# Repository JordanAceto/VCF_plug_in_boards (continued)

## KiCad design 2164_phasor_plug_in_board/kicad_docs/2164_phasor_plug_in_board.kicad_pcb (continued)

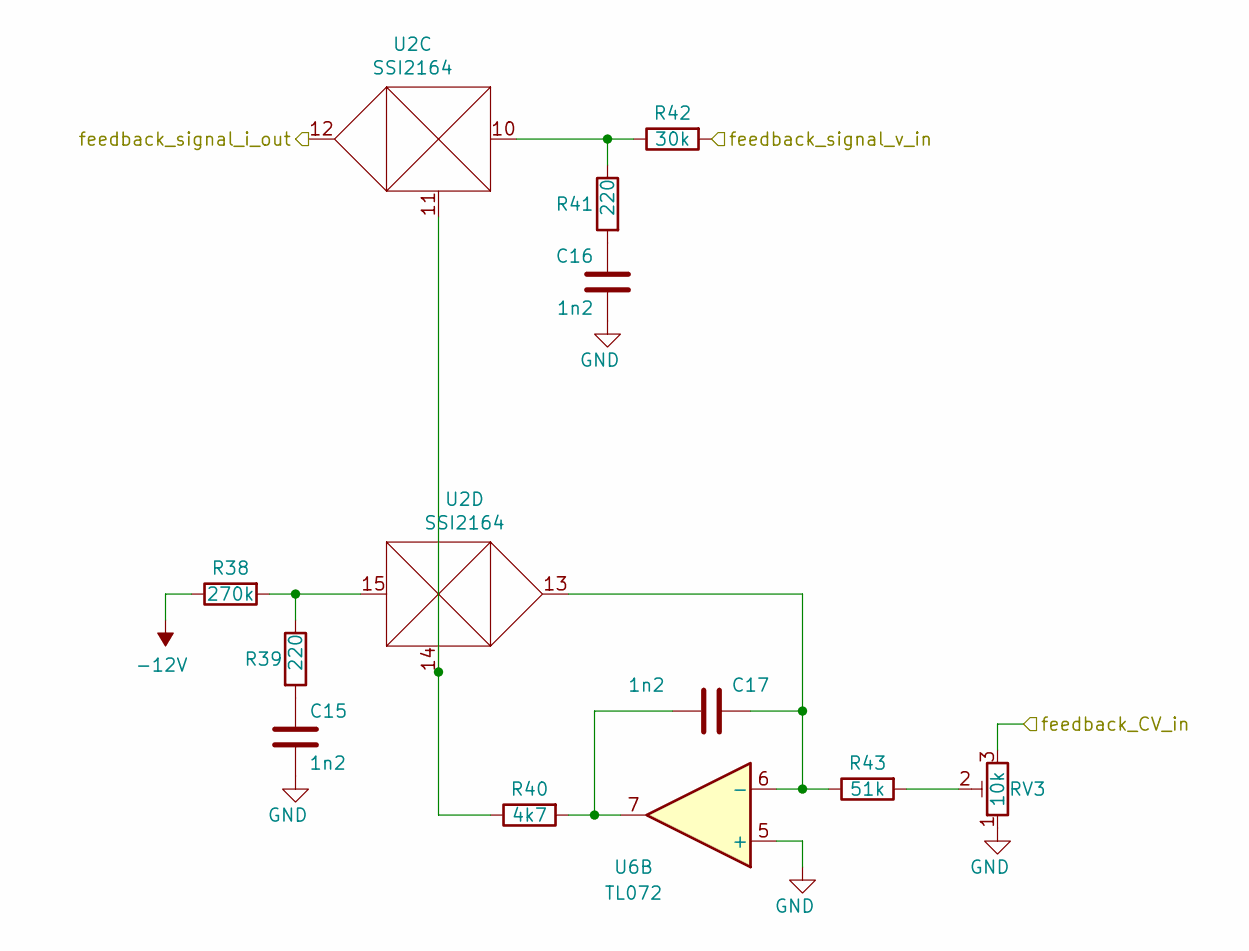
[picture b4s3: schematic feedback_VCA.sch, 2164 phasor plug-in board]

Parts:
C15, C16, C17: 1n2; C_0603_1608Metric
R38: 270k; R_0603_1608Metric
R39, R41: 220; R_0603_1608Metric
R40: 4k7; R_0603_1608Metric
R42: 30k; R_0603_1608Metric
R43: 51k; R_0603_1608Metric
RV3: 10k; Potentiometer_Bourns_3296W_Vertical
U2: SSI2164; SOIC-16_3.9x9.9mm_P1.27mm
U6: TL072; SOIC-8_3.9x4.9mm_P1.27mm

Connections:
-12V: R38.1; also elsewhere on the board
/feedback_VCA/feedback_CV_in: RV3.3; also elsewhere on the board
/feedback_VCA/feedback_signal_v_in: R42.2; also elsewhere on the board
/feedback_signal: U2.12; also elsewhere on the board
GND: C15.2, C16.2, RV3.1, U6.5 (+); also elsewhere on the board
unnamed: C15.1, R39.2
unnamed: C16.1, R41.2
unnamed: C17.1, R40.2, U6.7
unnamed: C17.2, R43.1, U2.13, U6.6 (-)
unnamed: R38.2, R39.1, U2.15
unnamed: R40.1, U2.11, U2.14
unnamed: R41.1, R42.1, U2.10
unnamed: R43.2, RV3.2

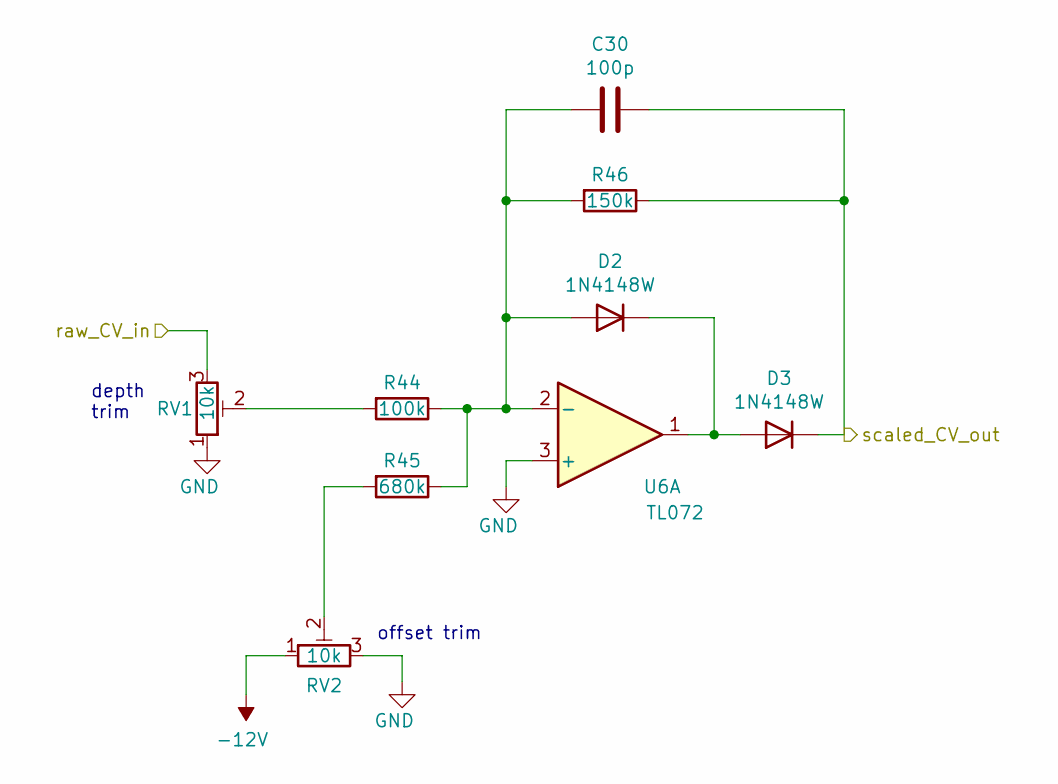
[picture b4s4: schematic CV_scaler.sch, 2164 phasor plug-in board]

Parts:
C30: 100p; C_0603_1608Metric
D2, D3: 1N4148W; D_SOD-123
R44: 100k; R_0603_1608Metric
R45: 680k; R_0603_1608Metric
R46: 150k; R_0603_1608Metric
RV1, RV2: 10k; Potentiometer_Bourns_3296W_Vertical
U6: TL072; SOIC-8_3.9x4.9mm_P1.27mm

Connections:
-12V: RV2.1; also elsewhere on the board
/CV_scaler/raw_CV_in: RV1.3; also elsewhere on the board
/all_pass_stages/Vfc_in: C30.1, D3.1 (K), R46.1; also elsewhere on the board
GND: RV1.1, RV2.3, U6.3 (+); also elsewhere on the board
unnamed: C30.2, D2.2 (A), R44.1, R45.1, R46.2, U6.2 (-)
unnamed: D2.1 (K), D3.2 (A), U6.1
unnamed: R44.2, RV1.2
unnamed: R45.2, RV2.2

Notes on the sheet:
offset trim
depth trim

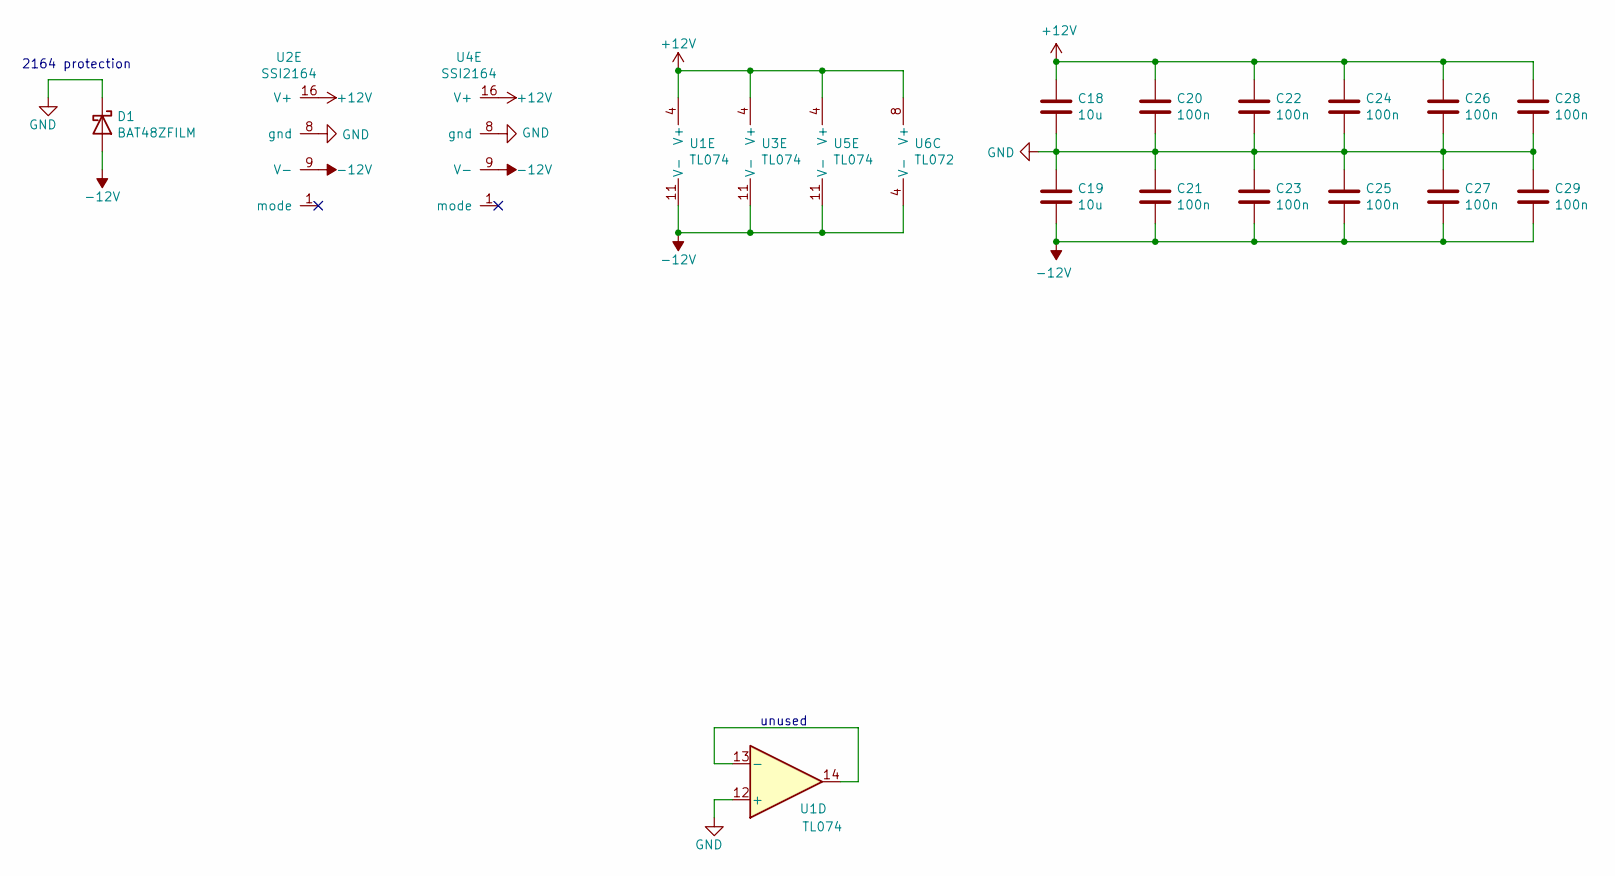
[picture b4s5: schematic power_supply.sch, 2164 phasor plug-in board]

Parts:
C18, C19: 10u; C_0805_2012Metric
C20, C21, C22, C23, C24, C25, C26, C27, C28, C29: 100n; C_0603_1608Metric
D1: BAT48ZFILM; D_SOD-123
U1, U3, U5: TL074; TSSOP-14_4.4x5mm_P0.65mm
U2, U4: SSI2164; SOIC-16_3.9x9.9mm_P1.27mm
U6: TL072; SOIC-8_3.9x4.9mm_P1.27mm

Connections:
+12V: C18.1, C20.1, C22.1, C24.1, C26.1, C28.1, U1.4 (V+), U2.16 (V+), U3.4 (V+), U4.16 (V+), U5.4 (V+), U6.8 (V+); also elsewhere on the board
-12V: C19.2, C21.2, C23.2, C25.2, C27.2, C29.2, D1.2 (A), U1.11 (V-), U2.9 (V-), U3.11 (V-), U4.9 (V-), U5.11 (V-), U6.4 (V-); also elsewhere on the board
GND: C18.2, C19.1, C20.2, C21.1, C22.2, C23.1, C24.2, C25.1, C26.2, C27.1, C28.2, C29.1, D1.1 (K), U1.12 (+), U2.8 (gnd), U4.8 (gnd); also elsewhere on the board
unnamed: U1.13 (-), U1.14

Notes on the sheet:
2164 protection
unused

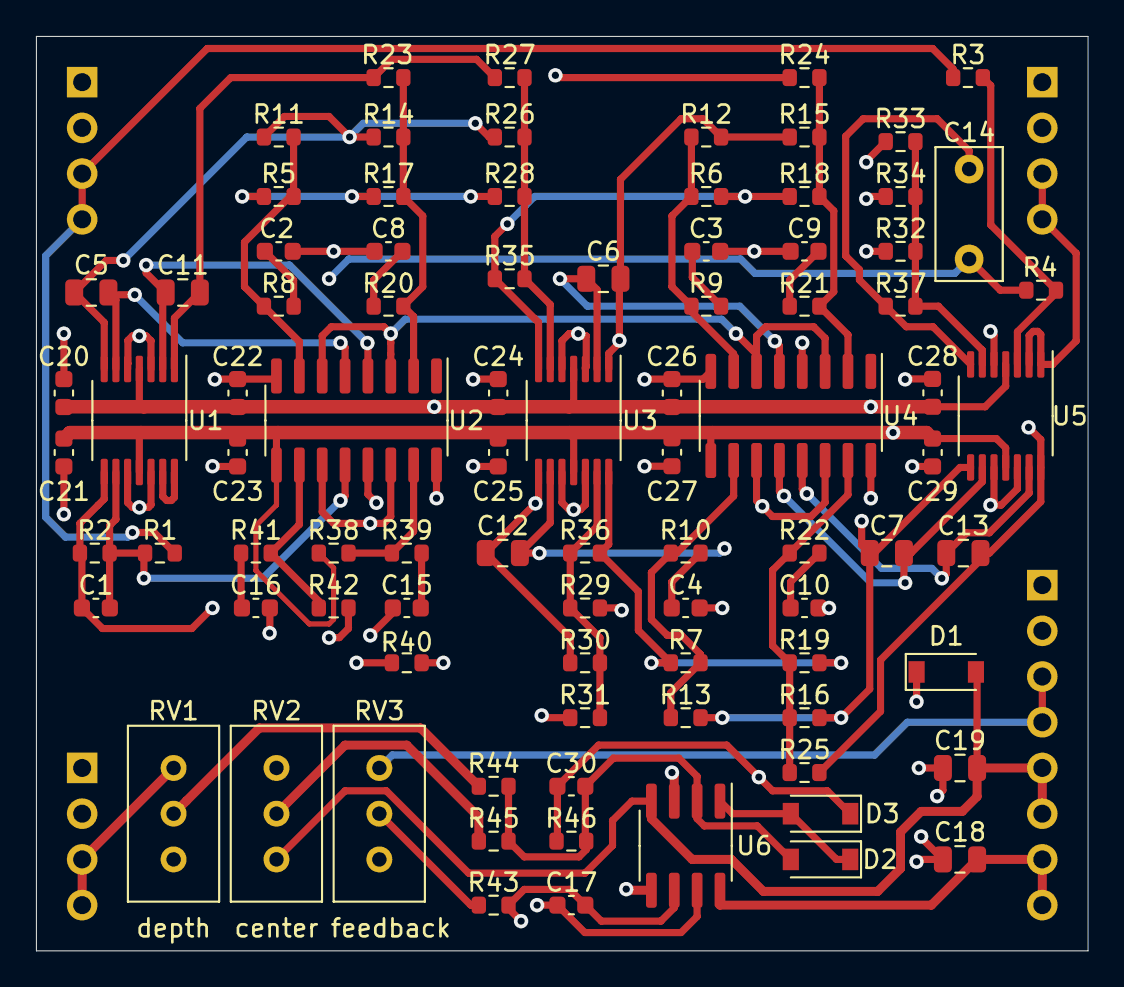
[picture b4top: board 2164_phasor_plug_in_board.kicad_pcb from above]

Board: 4 copper layers, 58.4 x 50.8 mm, 92 parts (0 on the bottom side), 55 nets.

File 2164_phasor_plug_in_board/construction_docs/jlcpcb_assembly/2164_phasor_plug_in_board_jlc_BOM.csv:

Comment,Designator,Footprint,LCSC Part Number
100k,"R46,R44",R_0603_1608Metric,C25803
330k,R45,R_0603_1608Metric,C23137
51k,R43,R_0603_1608Metric,C23196
30k,"R42,R25,R24,R23,R19,R18,R17,R13,R12,R11,R7,R6,R5,R3,R2,R1",R_0603_1608Metric,C22984
220,"R41,R39,R22,R21,R20,R10,R9,R8",R_0603_1608Metric,C22962
4k7,R40,R_0603_1608Metric,C23162
270k,R38,R_0603_1608Metric,C22965
20k,"R37,R36,R35,R34,R31,R28",R_0603_1608Metric,C4184
10k,"R33,R32,R30,R29,R27,R26",R_0603_1608Metric,C25804
15k,"R16,R15,R14",R_0603_1608Metric,C22809
12k,R4,R_0603_1608Metric,C22790
470p,C1,C_0603_1608Metric,C1620
1n2,"C30,C17,C16,C15,C10,C9,C8,C4,C3,C2",C_0603_1608Metric,C30615
100n,"C29,C28,C27,C26,C25,C24,C23,C22,C21,C20",C_0603_1608Metric,C14663
10u,"C19,C18",C_0805_2012Metric,C15850
TL072,U6,SOIC-8_3.9x4.9mm_P1.27mm,C6961
TL074,"U5,U3,U1",TSSOP-14_4.4x5mm_P0.65mm,C96507
1N4148W,"D2, D3",SOD-123,C81598

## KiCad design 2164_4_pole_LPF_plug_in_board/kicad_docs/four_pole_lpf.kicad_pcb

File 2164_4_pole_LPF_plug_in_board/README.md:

## SSI2164 4-pole Low Pass Filter plug-in board

Small SSI2164 based low pass filter PCB, designed to plug into a larger motherboard.

## Details

This pcb uses the 4-pole band-pass feedback as a means of Q-compensation as outlined in application note AN701.

Voltage controlled feedback is provided, consistent with the other filter plug-in boards.

Construction documents for the low cost pcb assembly service from JLCPCB are included. A few parts are not included in the assembly documents, such as the through hole components, the SSI2164 chips, and also the 220pf timing capacitors for the filter stages. These are left to the builder to install. These should be good quality C0G/NP0 0805 capacitors with 2% or better tolerance.

There are also footprints for optional capacitors across the feedback amplifier gain setting resistors (C9 and C13). Placing small value capacitors here can tame excessive feedback at high frequencies, or address instability if it is observed.

## Inputs

-Audio in: dry audio input to be filtered.

-Frequency CV in: 0 volts to +2.048 volts, higher voltage = higher sweep.

-Feedback CV in: 0 volts to +2.048 volts, higher voltage = more feedback.

## Outputs

-Audio out: filtered audio output.

## Power Supply Requirements

A bipolar 12 volt power supply is required. This will typically come from the motherboard.

## Calibration

- See the top level README for calibration instructions.

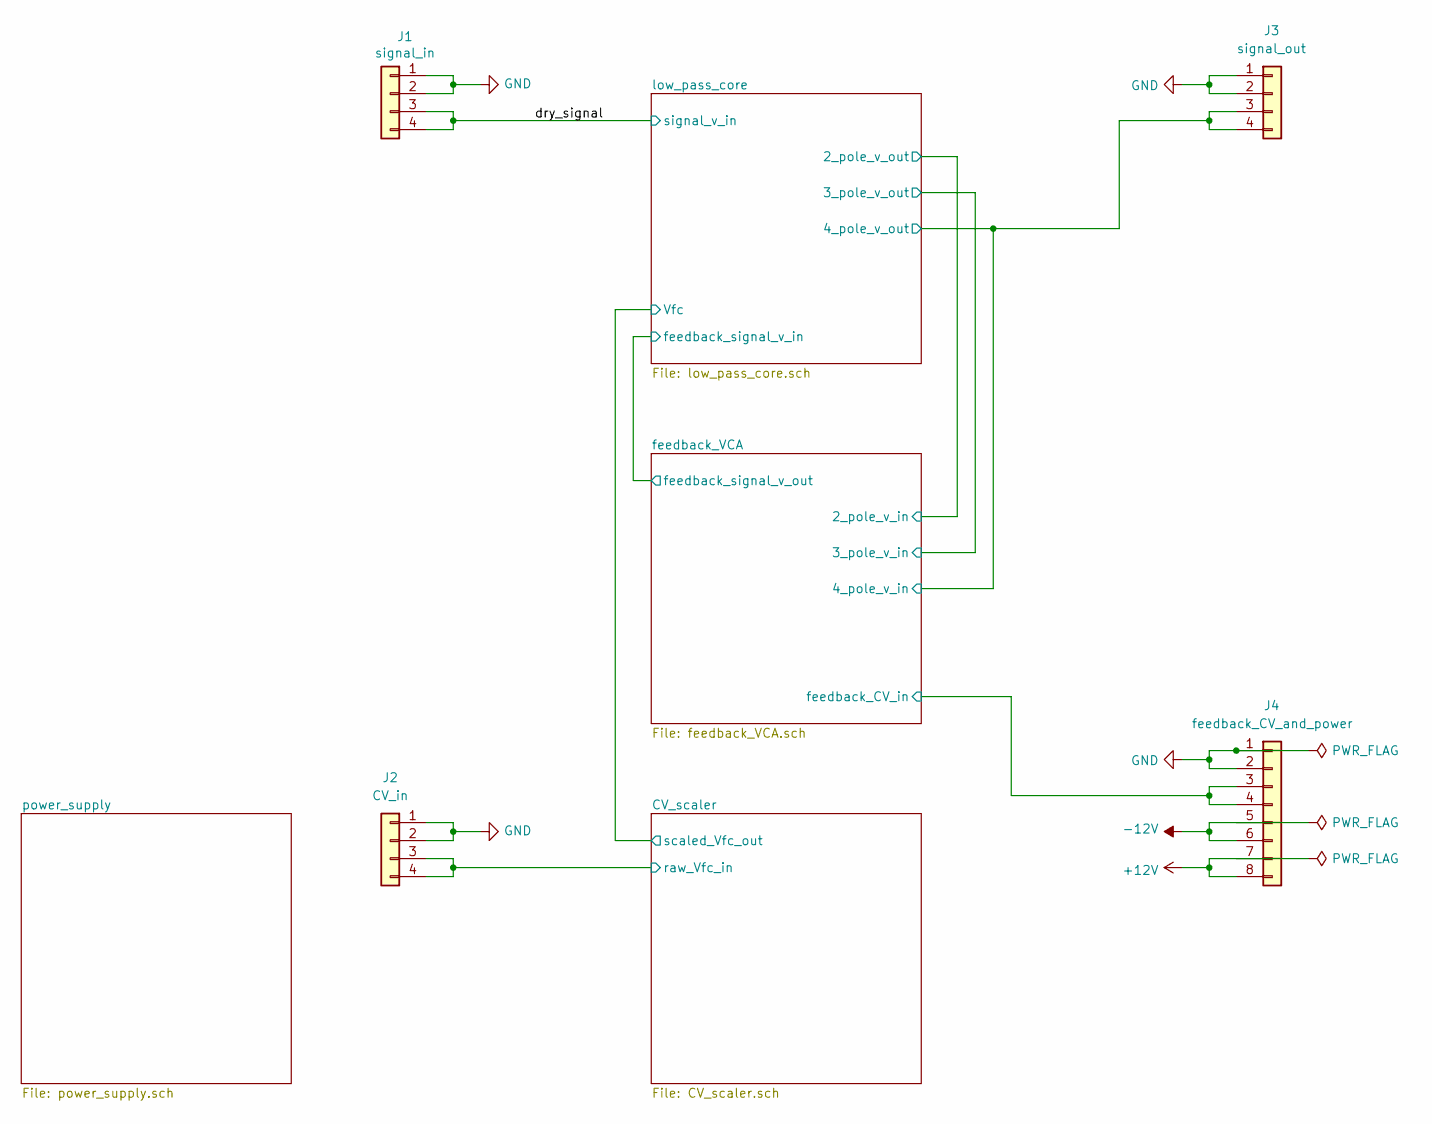
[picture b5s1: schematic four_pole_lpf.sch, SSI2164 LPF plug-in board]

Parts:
J1: signal_in; PinHeader_1x04_P2.54mm_Vertical
J2: CV_in; PinHeader_1x04_P2.54mm_Vertical
J3: signal_out; PinHeader_1x04_P2.54mm_Vertical
J4: feedback_CV_and_power; PinHeader_1x08_P2.54mm_Vertical

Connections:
+12V: J4.7, J4.8; also elsewhere on the board
-12V: J4.5, J4.6; also elsewhere on the board
/CV_scaler/raw_Vfc_in: J2.3, J2.4; also elsewhere on the board
/dry_signal: J1.3, J1.4; also elsewhere on the board
/feedback_VCA/4_pole_v_in: J3.3, J3.4; also elsewhere on the board
/feedback_VCA/feedback_CV_in: J4.3, J4.4; also elsewhere on the board
GND: J1.1, J1.2, J2.1, J2.2, J3.1, J3.2, J4.1, J4.2; also elsewhere on the board

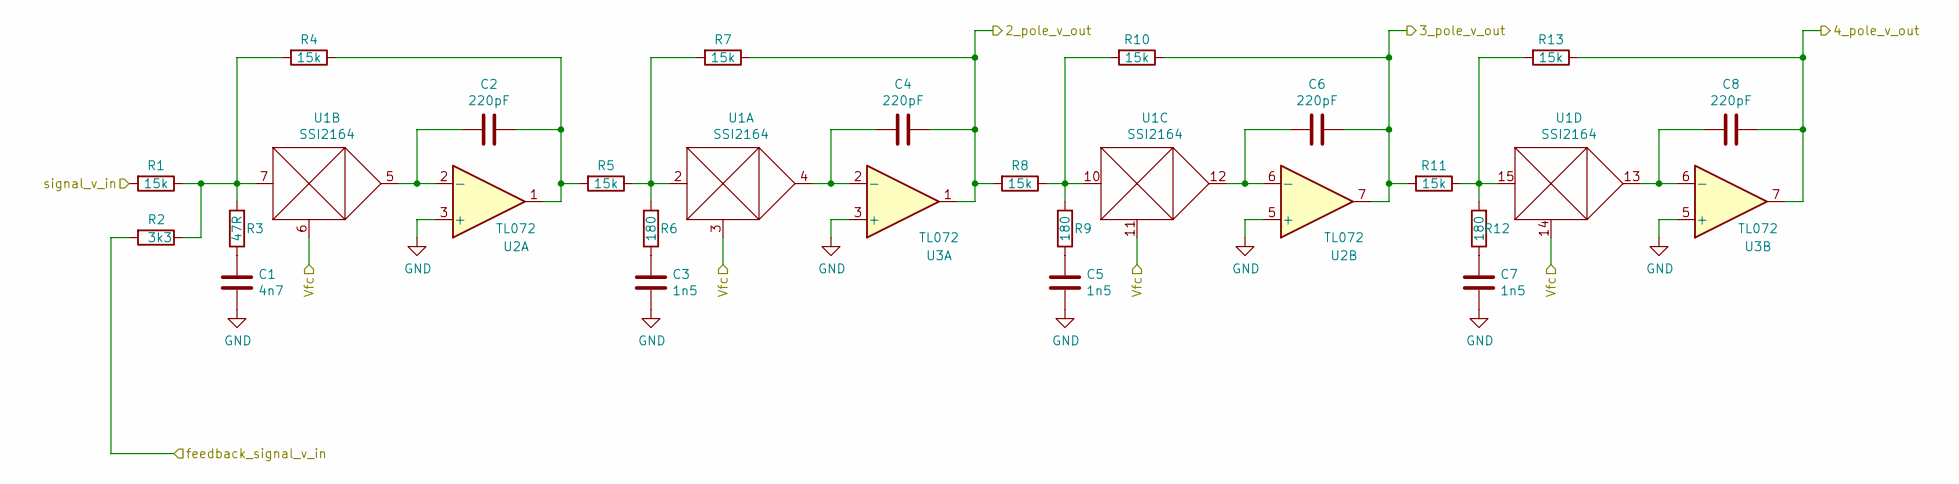
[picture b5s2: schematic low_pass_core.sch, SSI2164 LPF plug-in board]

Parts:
C1: 4n7; C_0603_1608Metric
C2, C4, C6, C8: 220pF; C_0805_2012Metric
C3, C5, C7: 1n5; C_0603_1608Metric
R1, R4, R5, R7, R8, R10, R11, R13: 15k; R_0603_1608Metric
R2: 3k3; R_0603_1608Metric
R3: 47R; R_0603_1608Metric
R6, R9, R12: 180; R_0603_1608Metric
U1: SSI2164; SOIC-16_3.9x9.9mm_P1.27mm
U2, U3: TL072; SOIC-8_3.9x4.9mm_P1.27mm

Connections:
/dry_signal: R1.2; also elsewhere on the board
/feedback_VCA/2_pole_v_in: C4.1, R7.1, R8.2, U3.1; also elsewhere on the board
/feedback_VCA/3_pole_v_in: C6.1, R10.1, R11.2, U2.7; also elsewhere on the board
/feedback_VCA/4_pole_v_in: C8.1, R13.1, U3.7; also elsewhere on the board
/low_pass_core/Vfc: U1.3, U1.6, U1.11, U1.14; also elsewhere on the board
/low_pass_core/feedback_signal_v_in: R2.2; also elsewhere on the board
GND: C1.1, C3.1, C5.1, C7.1, U2.3 (+), U2.5 (+), U3.3 (+), U3.5 (+); also elsewhere on the board
unnamed: C1.2, R3.1
unnamed: C2.1, R4.1, R5.2, U2.1
unnamed: C2.2, U1.5, U2.2 (-)
unnamed: C3.2, R6.1
unnamed: C4.2, U1.4, U3.2 (-)
unnamed: C5.2, R9.1
unnamed: C6.2, U1.12, U2.6 (-)
unnamed: C7.2, R12.1
unnamed: C8.2, U1.13, U3.6 (-)
unnamed: R1.1, R2.1, R3.2, R4.2, U1.7
unnamed: R5.1, R6.2, R7.2, U1.2
unnamed: R8.1, R9.2, R10.2, U1.10
unnamed: R11.1, R12.2, R13.2, U1.15

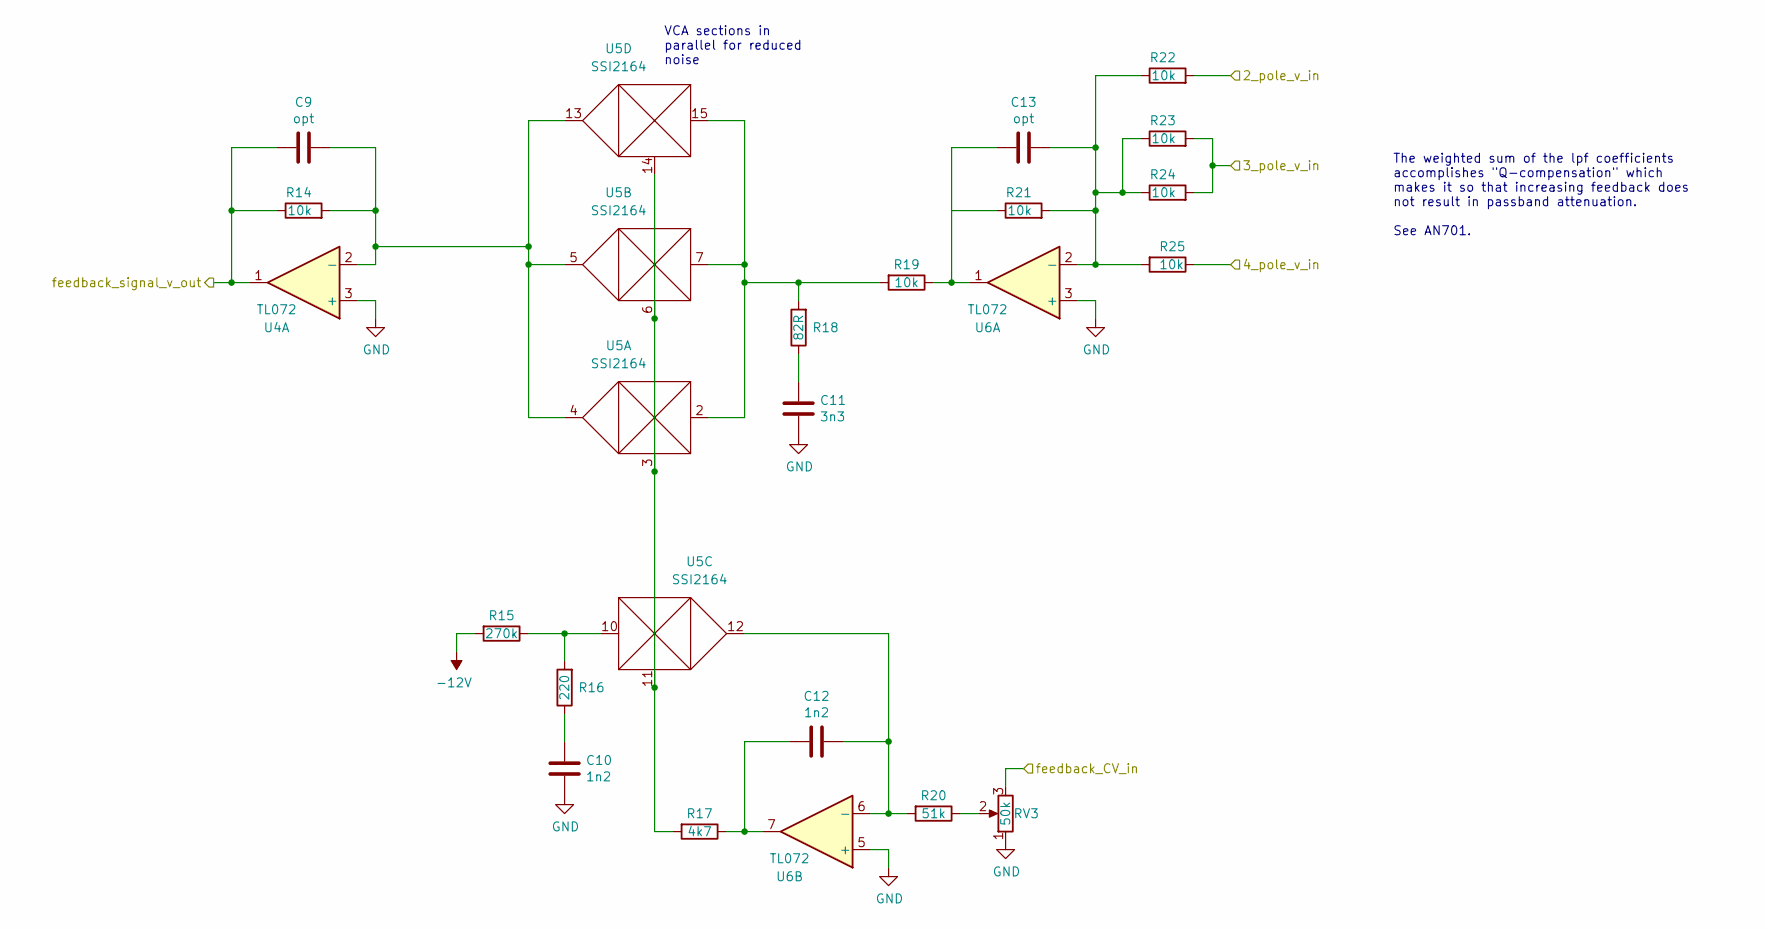
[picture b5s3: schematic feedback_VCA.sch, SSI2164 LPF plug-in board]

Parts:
C9, C13: opt; C_0805_2012Metric
C10, C12: 1n2; C_0603_1608Metric
C11: 3n3; C_0603_1608Metric
R14, R19, R21, R22, R23, R24, R25: 10k; R_0603_1608Metric
R15: 270k; R_0603_1608Metric
R16: 220; R_0603_1608Metric
R17: 4k7; R_0603_1608Metric
R18: 82R; R_0603_1608Metric
R20: 51k; R_0603_1608Metric
RV3: 50k; Potentiometer_Bourns_3296W_Vertical
U4, U6: TL072; SOIC-8_3.9x4.9mm_P1.27mm
U5: SSI2164; SOIC-16_3.9x9.9mm_P1.27mm

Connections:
-12V: R15.2; also elsewhere on the board
/feedback_VCA/2_pole_v_in: R22.2; also elsewhere on the board
/feedback_VCA/3_pole_v_in: R23.2, R24.2; also elsewhere on the board
/feedback_VCA/4_pole_v_in: R25.1; also elsewhere on the board
/feedback_VCA/feedback_CV_in: RV3.3; also elsewhere on the board
/low_pass_core/feedback_signal_v_in: C9.2, R14.1, U4.1; also elsewhere on the board
GND: C10.1, C11.1, RV3.1, U4.3 (+), U6.3 (+), U6.5 (+); also elsewhere on the board
unnamed: C9.1, R14.2, U4.2 (-), U5.4, U5.5, U5.13
unnamed: C10.2, R16.1
unnamed: C11.2, R18.1
unnamed: C12.1, R20.2, U5.12, U6.6 (-)
unnamed: C12.2, R17.1, U6.7
unnamed: C13.1, R21.2, R22.1, R23.1, R24.1, R25.2, U6.2 (-)
unnamed: C13.2, R19.1, R21.1, U6.1
unnamed: R15.1, R16.2, U5.10
unnamed: R17.2, U5.3, U5.6, U5.11, U5.14
unnamed: R18.2, R19.2, U5.2, U5.7, U5.15
unnamed: R20.1, RV3.2

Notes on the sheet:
The weighted sum of the lpf coefficients accomplishes "Q-compensation" which makes it so that increasing feedback does not result in passband attenuation. See AN701.
VCA sections in parallel for reduced noise

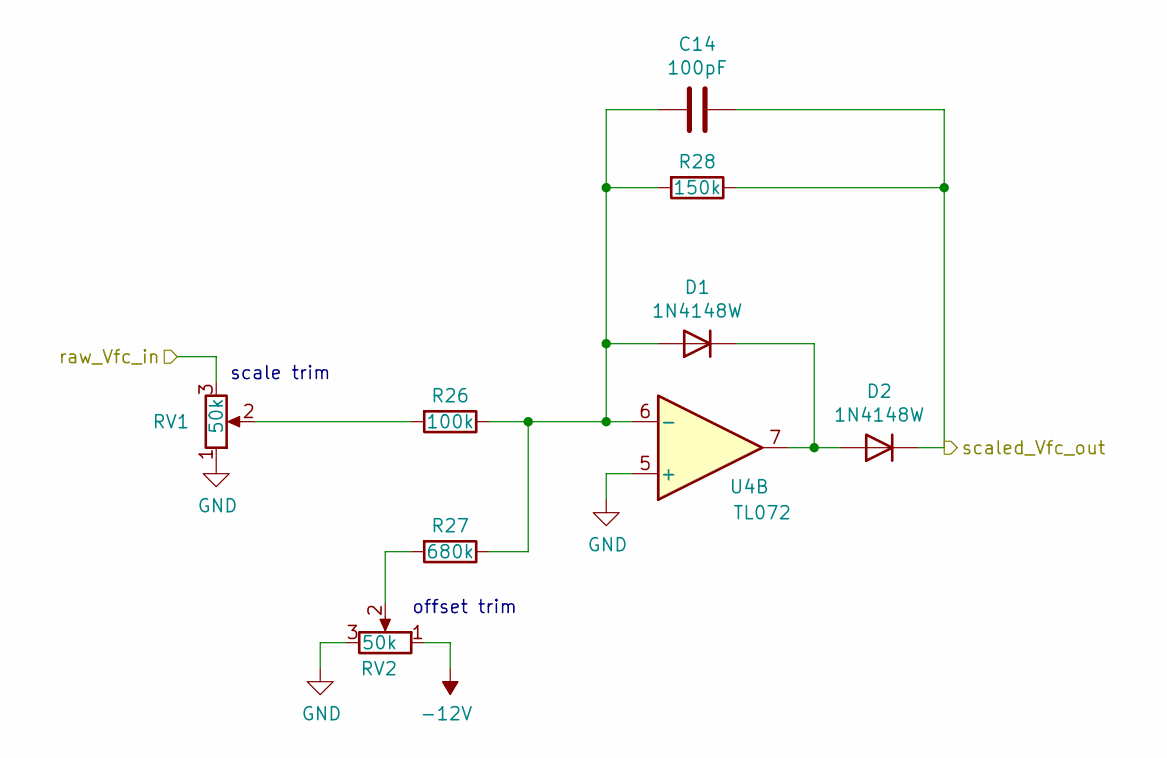
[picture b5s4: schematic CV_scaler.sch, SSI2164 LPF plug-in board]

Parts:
C14: 100pF; C_0603_1608Metric
D1, D2: 1N4148W; D_SOD-123
R26: 100k; R_0603_1608Metric
R27: 680k; R_0603_1608Metric
R28: 150k; R_0603_1608Metric
RV1, RV2: 50k; Potentiometer_Bourns_3296W_Vertical
U4: TL072; SOIC-8_3.9x4.9mm_P1.27mm

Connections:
-12V: RV2.1; also elsewhere on the board
/CV_scaler/raw_Vfc_in: RV1.3; also elsewhere on the board
/low_pass_core/Vfc: C14.1, D2.1 (K), R28.1; also elsewhere on the board
GND: RV1.1, RV2.3, U4.5 (+); also elsewhere on the board
unnamed: C14.2, D1.2 (A), R26.1, R27.1, R28.2, U4.6 (-)
unnamed: D1.1 (K), D2.2 (A), U4.7
unnamed: R26.2, RV1.2
unnamed: R27.2, RV2.2

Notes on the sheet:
scale trim
offset trim

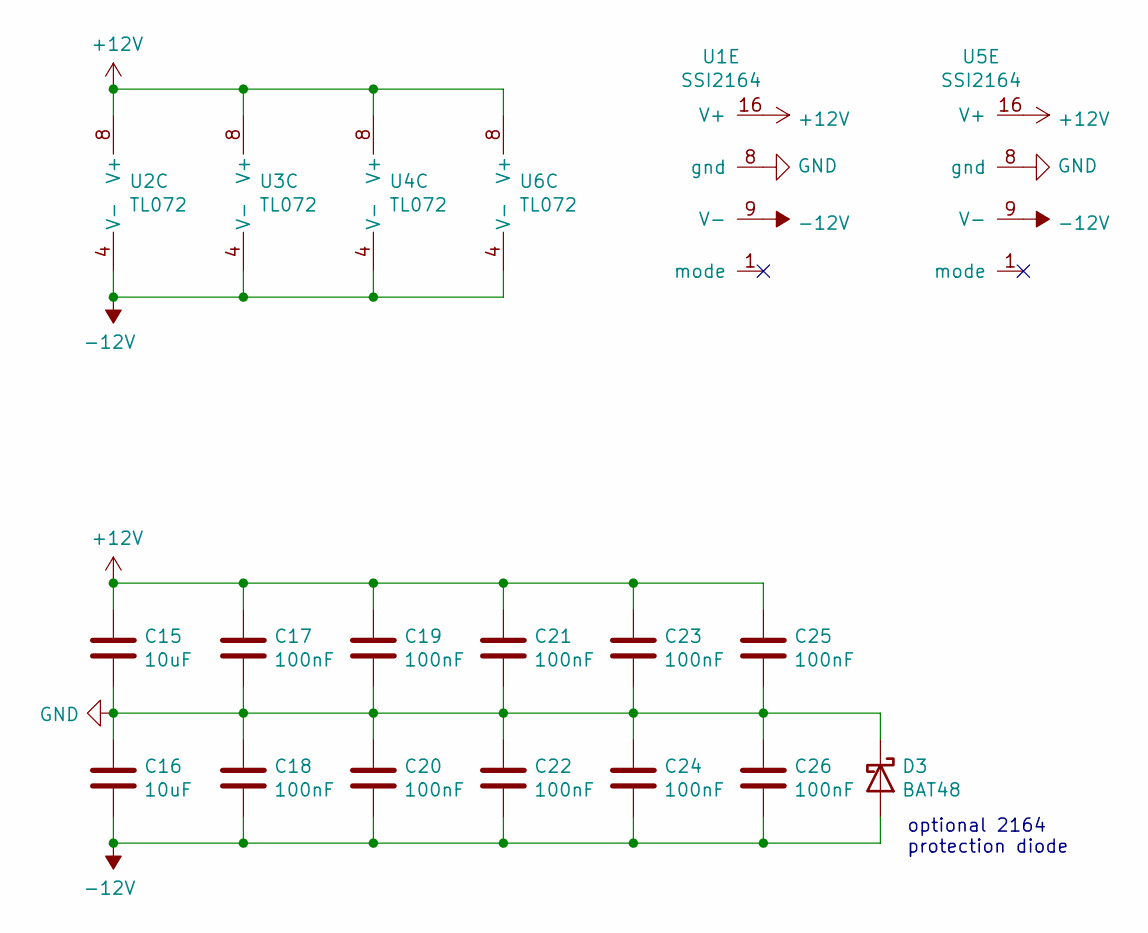
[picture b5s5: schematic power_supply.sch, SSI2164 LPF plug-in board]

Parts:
C15, C16: 10uF; C_0805_2012Metric
C17, C18, C19, C20, C21, C22, C23, C24, C25, C26: 100nF; C_0603_1608Metric
D3: BAT48; D_SOD-123
U1, U5: SSI2164; SOIC-16_3.9x9.9mm_P1.27mm
U2, U3, U4, U6: TL072; SOIC-8_3.9x4.9mm_P1.27mm

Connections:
+12V: C15.1, C17.1, C19.1, C21.1, C23.1, C25.1, U1.16 (V+), U2.8 (V+), U3.8 (V+), U4.8 (V+), U5.16 (V+), U6.8 (V+); also elsewhere on the board
-12V: C16.2, C18.2, C20.2, C22.2, C24.2, C26.2, D3.2 (A), U1.9 (V-), U2.4 (V-), U3.4 (V-), U4.4 (V-), U5.9 (V-), U6.4 (V-); also elsewhere on the board
GND: C15.2, C16.1, C17.2, C18.1, C19.2, C20.1, C21.2, C22.1, C23.2, C24.1, C25.2, C26.1, D3.1 (K), U1.8 (gnd), U5.8 (gnd); also elsewhere on the board

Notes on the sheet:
optional 2164 protection diode

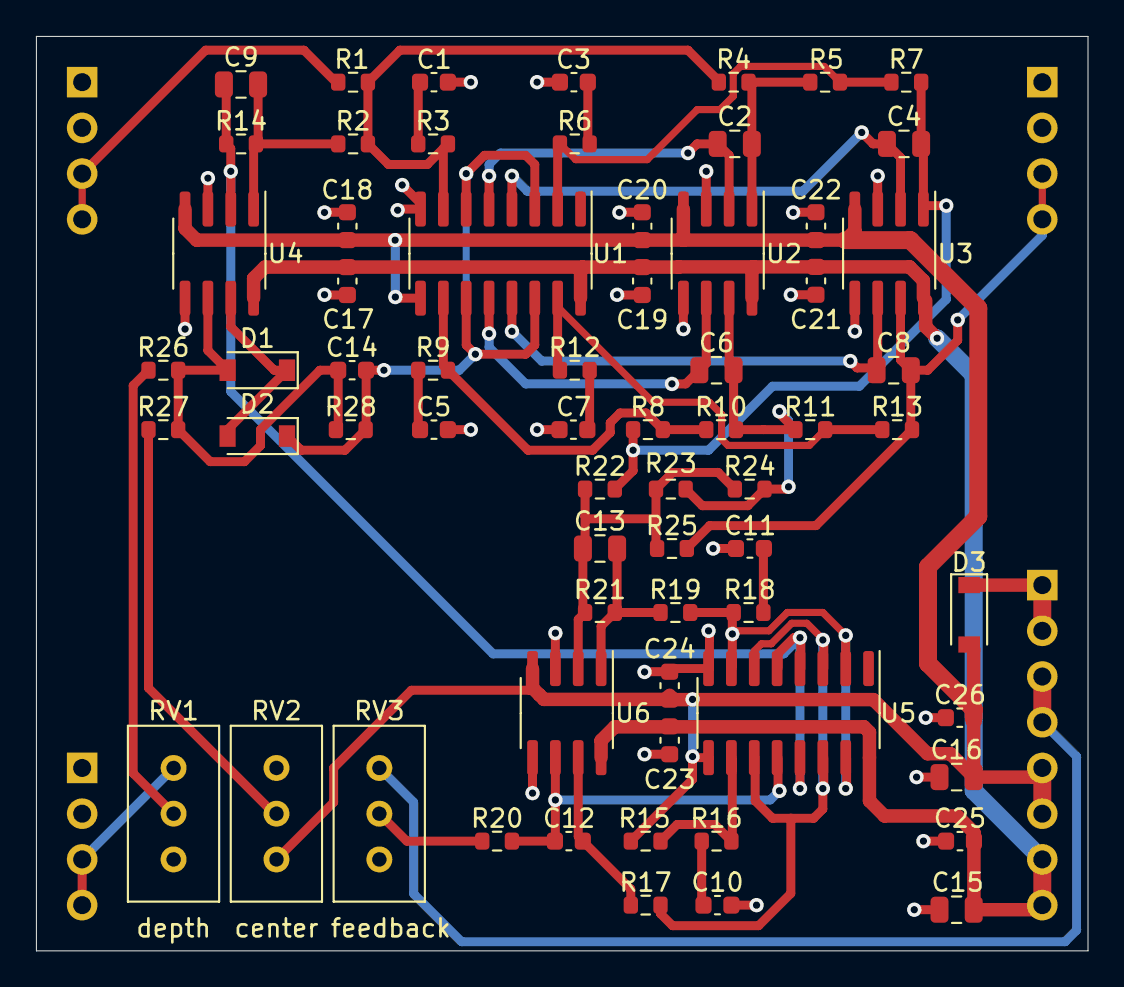
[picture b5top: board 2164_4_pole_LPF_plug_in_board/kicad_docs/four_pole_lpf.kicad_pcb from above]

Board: 4 copper layers, 58.4 x 50.8 mm, 70 parts (0 on the bottom side), 39 nets.

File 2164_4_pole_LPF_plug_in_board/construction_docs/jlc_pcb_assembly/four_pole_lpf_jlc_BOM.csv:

Comment,Designator,Footprint,LCSC Part Number
TL072,"U6,U4,U3,U2",SOIC-8_3.9x4.9mm_P1.27mm,C6961
10k,"R23,R25,R24,R22,R21, R14, R19",R_0603_1608Metric,C25804
51k,R20,R_0603_1608Metric,C23196
82R,R18,R_0603_1608Metric,C23255
4k7,R17,R_0603_1608Metric,C23162
220,R16,R_0603_1608Metric,C22962
270k,R15,R_0603_1608Metric,C22965
150k,R28,R_0603_1608Metric,C22807
680k,R27,R_0603_1608Metric,C25822
100k,R26,R_0603_1608Metric,C25803
15k,"R13,R11,R10,R8,R7,R5,R4,R1",R_0603_1608Metric,C22809
180,"R12,R9,R6",R_0603_1608Metric,C22828
47R,R3,R_0603_1608Metric,C23182
3k3,R2,R_0603_1608Metric,C22978
1N4148W,"D2,D1",D_SOD-123,C81598
1n2,"C12,C10",C_0603_1608Metric,C30615
3n3,C11,C_0603_1608Metric,C1613
100nF,"C26,C25,C24,C23,C22,C21,C20,C19,C18,C17",C_0603_1608Metric,C14663
10uF,"C16,C15",C_0805_2012Metric,C15850
100pF,C14,C_0603_1608Metric,C14858
1n5,"C7,C5,C3",C_0603_1608Metric,C1595
4n7,C1,C_0603_1608Metric,C53987

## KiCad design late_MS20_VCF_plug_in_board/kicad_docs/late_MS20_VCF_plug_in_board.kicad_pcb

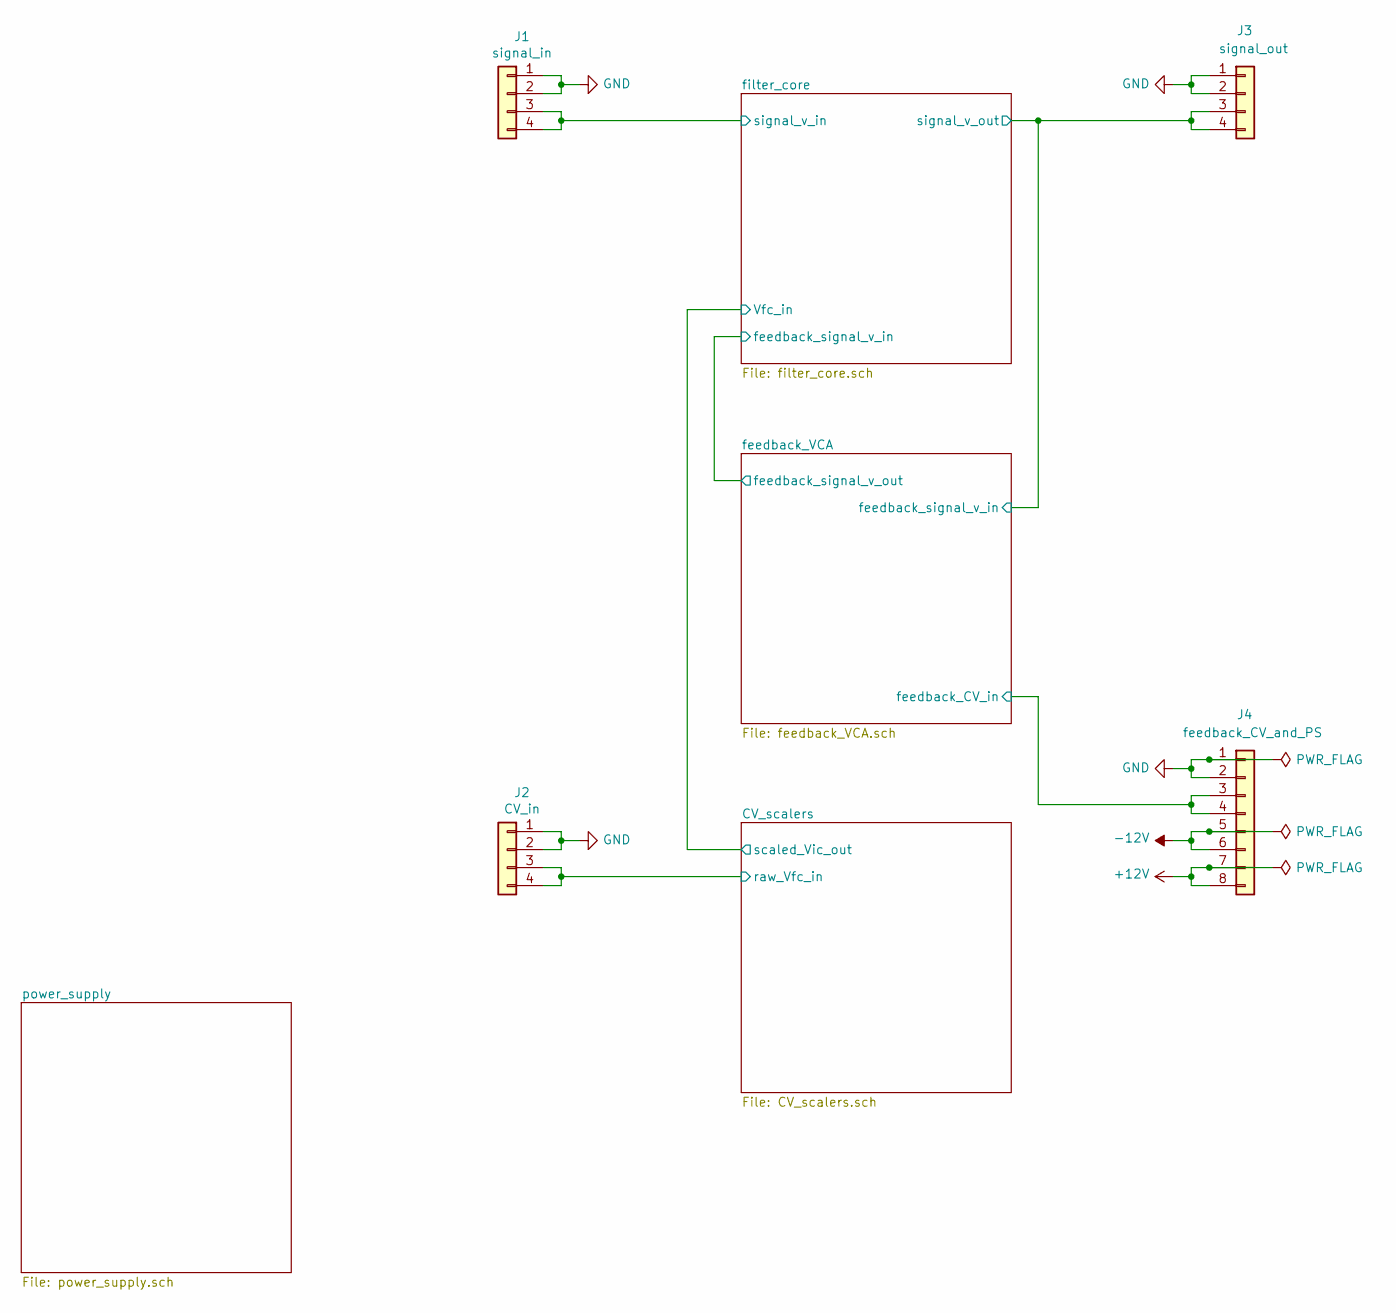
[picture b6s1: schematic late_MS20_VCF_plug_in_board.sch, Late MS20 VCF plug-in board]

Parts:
J1: signal_in; PinHeader_1x04_P2.54mm_Vertical
J2: CV_in; PinHeader_1x04_P2.54mm_Vertical
J3: signal_out; PinHeader_1x04_P2.54mm_Vertical
J4: feedback_CV_and_PS; PinHeader_1x08_P2.54mm_Vertical

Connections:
+12V: J4.7, J4.8; also elsewhere on the board
-12V: J4.5, J4.6; also elsewhere on the board
/CV_scalers/raw_Vfc_in: J2.3, J2.4; also elsewhere on the board
/feedback_VCA/feedback_CV_in: J4.3, J4.4; also elsewhere on the board
/feedback_VCA/feedback_signal_v_in: J3.3, J3.4; also elsewhere on the board
/filter_core/signal_v_in: J1.3, J1.4; also elsewhere on the board
GND: J1.1, J1.2, J2.1, J2.2, J3.1, J3.2, J4.1, J4.2; also elsewhere on the board

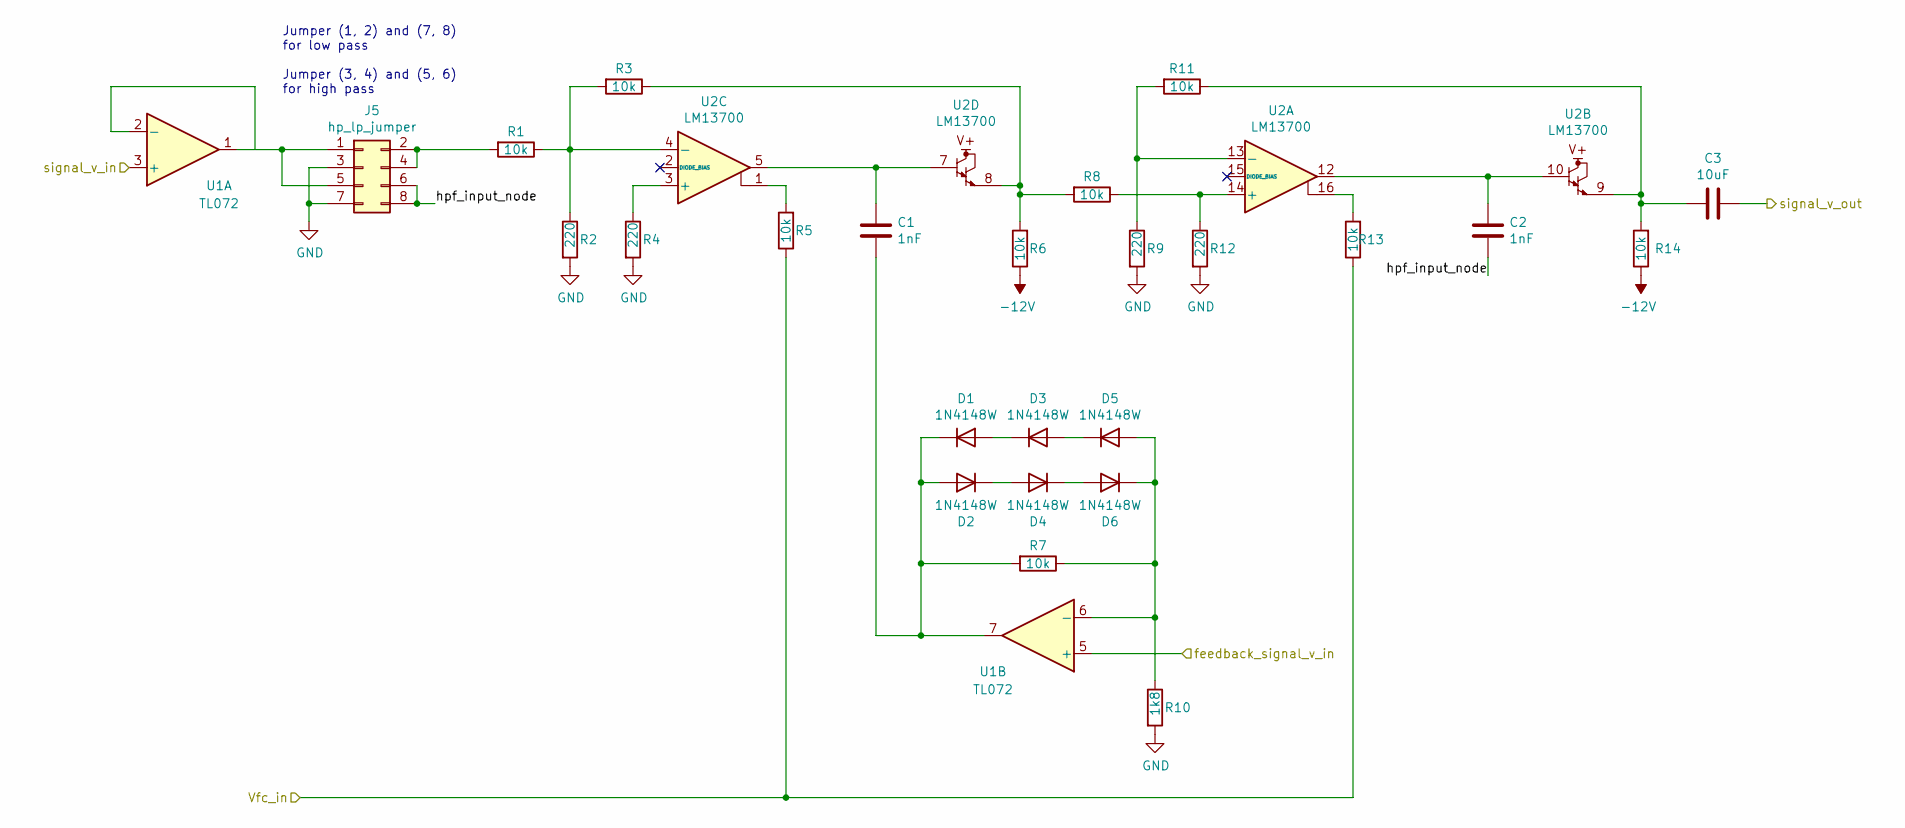
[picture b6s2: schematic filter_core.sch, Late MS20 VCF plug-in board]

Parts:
C1, C2: 1nF; C_0805_2012Metric_Pad1.15x1.40mm_HandSolder
C3: 10uF; C_Radial_D6.3mm_H5.0mm_P2.50mm
D1, D2, D3, D4, D5, D6: 1N4148W; D_SOD-123
J5: hp_lp_jumper; PinHeader_2x04_P2.54mm_Vertical
R1, R3, R5, R6, R7, R8, R11, R13, R14: 10k; R_0805_2012Metric_Pad1.15x1.40mm_HandSolder
R2, R4, R9, R12: 220; R_0805_2012Metric_Pad1.15x1.40mm_HandSolder
R10: 1k8; R_0805_2012Metric_Pad1.15x1.40mm_HandSolder
U1: TL072; SOIC-8_3.9x4.9mm_P1.27mm
U2: LM13700; SOIC-16_3.9x9.9mm_P1.27mm

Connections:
-12V: R6.1, R14.1; also elsewhere on the board
/feedback_VCA/feedback_signal_v_in: C3.1; also elsewhere on the board
/filter_core/Vfc_in: R5.1, R13.1; also elsewhere on the board
/filter_core/feedback_signal_v_in: U1.5 (+); also elsewhere on the board
/filter_core/hpf_input_node: C2.2, J5.6, J5.8
/filter_core/signal_v_in: U1.3 (+); also elsewhere on the board
GND: J5.3, J5.7, R2.2, R4.2, R9.2, R10.2, R12.2; also elsewhere on the board
unnamed: C1.1, U2.5, U2.7
unnamed: C1.2, D1.1 (K), D2.2 (A), R7.2, U1.7
unnamed: C2.1, U2.10, U2.12
unnamed: C3.2, R11.1, R14.2, U2.9
unnamed: D1.2 (A), D3.1 (K)
unnamed: D2.1 (K), D4.2 (A)
unnamed: D3.2 (A), D5.1 (K)
unnamed: D4.1 (K), D6.2 (A)
unnamed: D5.2 (A), D6.1 (K), R7.1, R10.1, U1.6 (-)
unnamed: J5.1, J5.5, U1.1, U1.2 (-)
unnamed: J5.2, J5.4, R1.2
unnamed: R1.1, R2.1, R3.2, U2.4 (-)
unnamed: R3.1, R6.2, R8.2, U2.8
unnamed: R4.1, U2.3 (+)
unnamed: R5.2, U2.1
unnamed: R9.1, R11.2, U2.13 (-)
unnamed: R8.1, R12.1, U2.14 (+)
unnamed: R13.2, U2.16

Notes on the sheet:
Jumper (1, 2) and (7, 8) for low pass Jumper (3, 4) and (5, 6) for high pass
